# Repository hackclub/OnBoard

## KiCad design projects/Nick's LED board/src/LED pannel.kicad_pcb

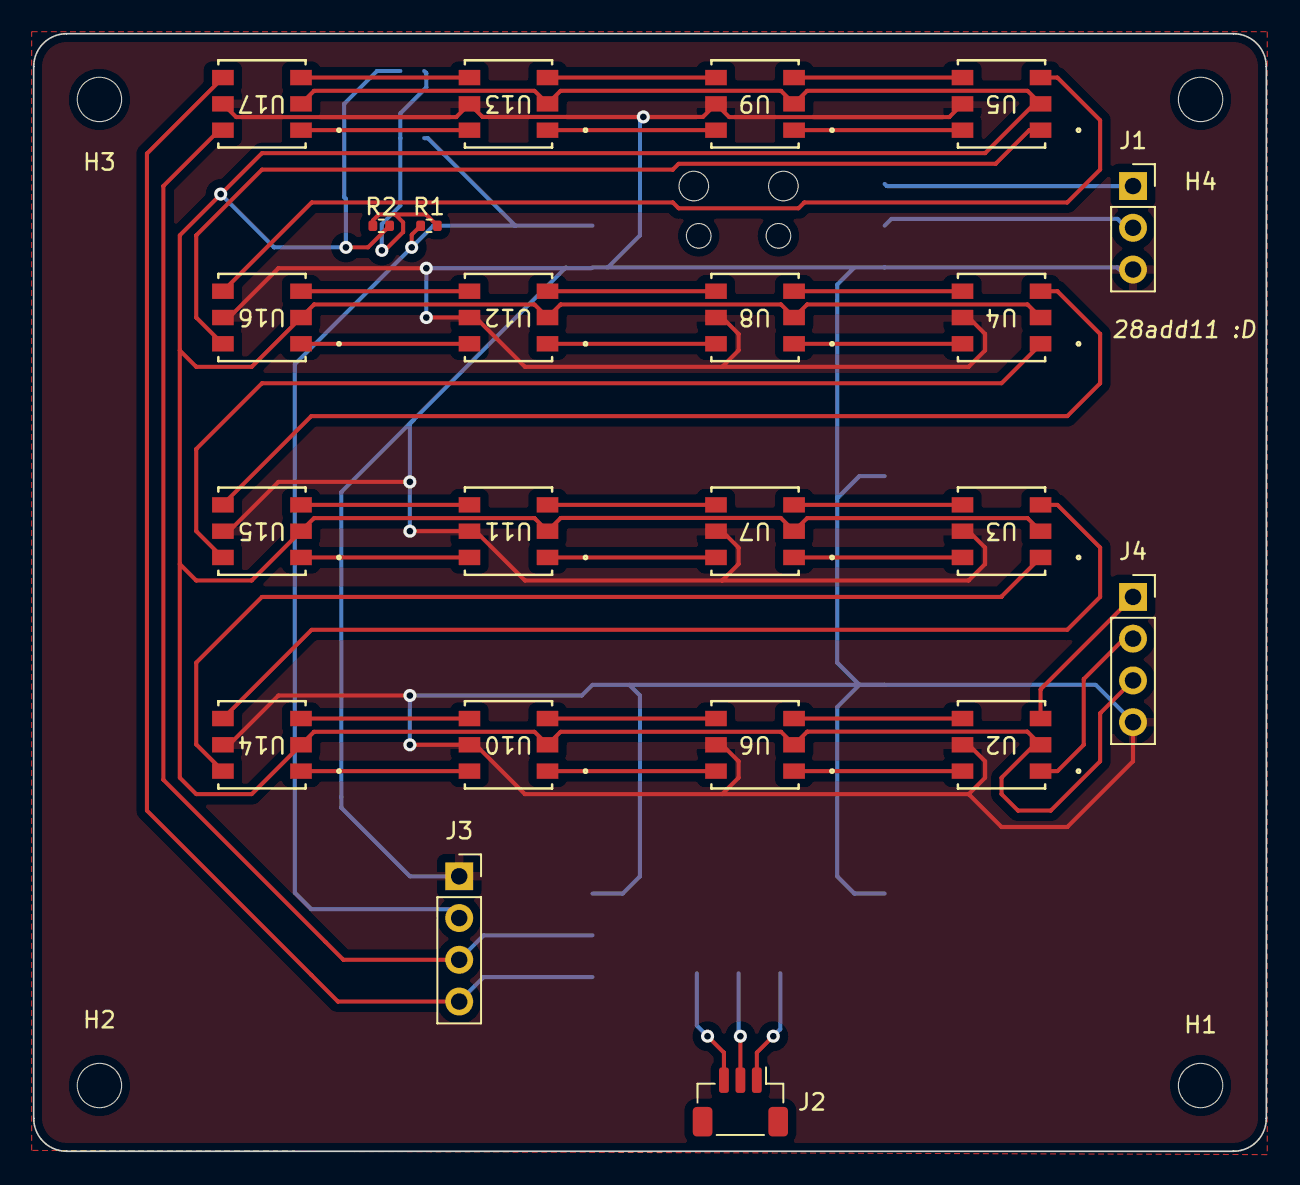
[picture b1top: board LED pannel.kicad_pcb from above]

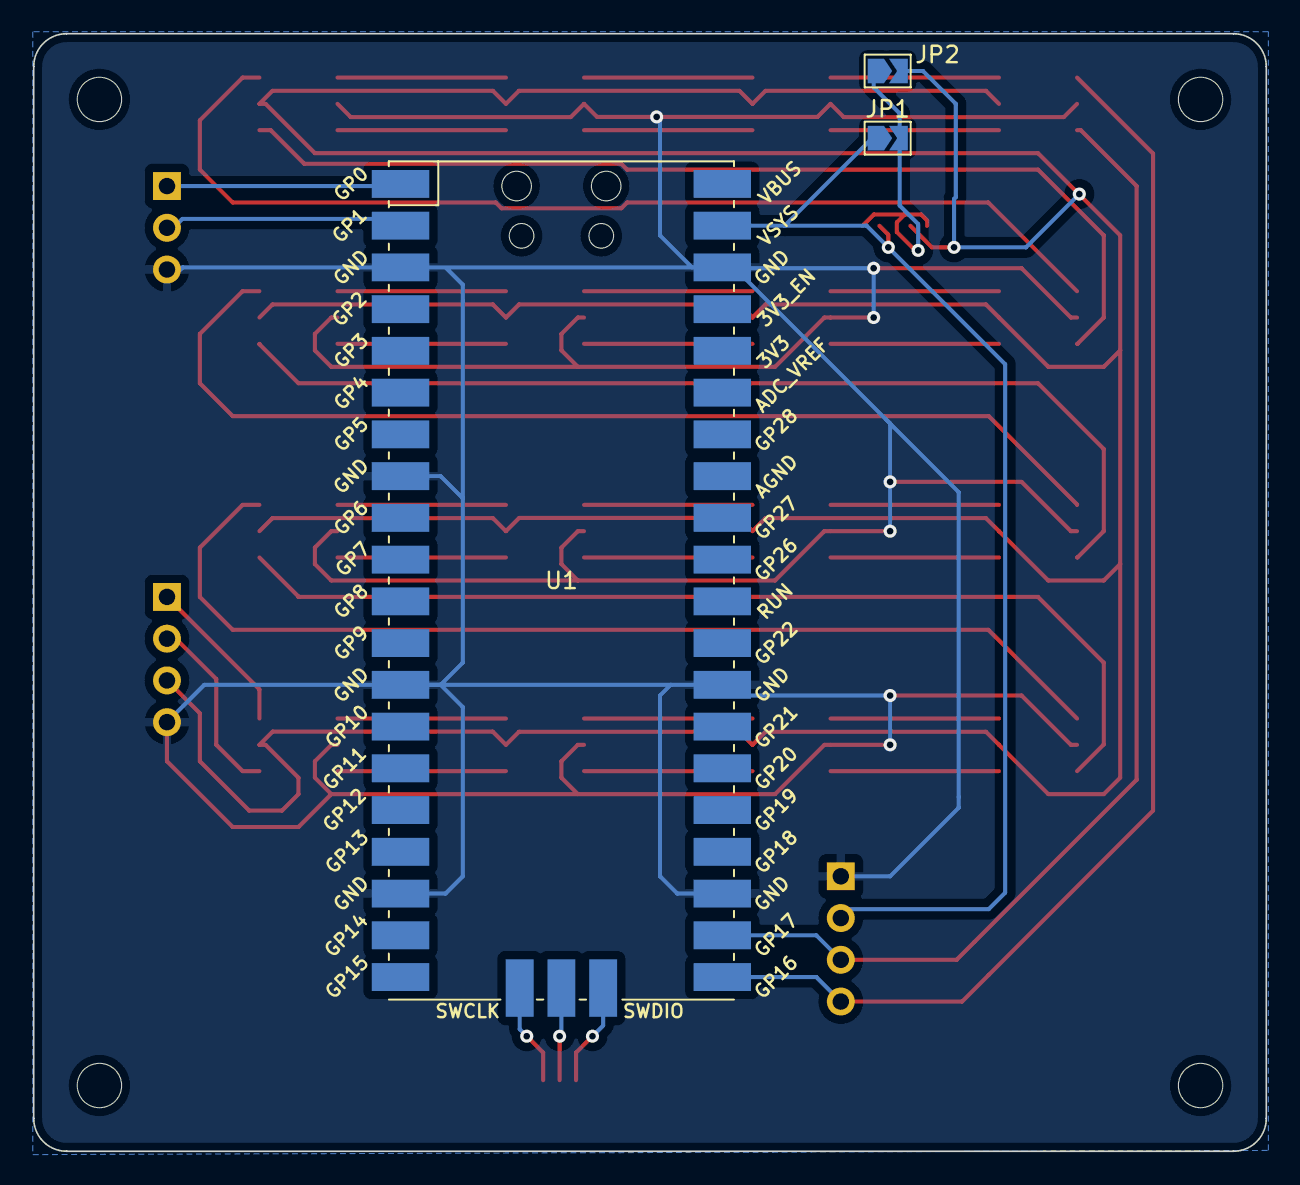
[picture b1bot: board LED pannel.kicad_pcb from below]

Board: 2 copper layers, 75.0 x 68.0 mm, 29 parts (3 on the bottom side), 43 nets.

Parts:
H1, H2, H3, H4: MountingHole; MountingHole_2.7mm
J1: Conn_01x03_Female; PinSocket_1x03_P2.54mm_Vertical
J2: Conn_01x03_Female; JST_SH_BM03B-SRSS-TB_1x03-1MP_P1.00mm_Vertical
J3, J4: Conn_01x04_Female; PinSocket_1x04_P2.54mm_Vertical
JP1, JP2: SolderJumper_2_Open; SolderJumper-2_P1.3mm_Open_TrianglePad1.0x1.5mm
R1, R2: 220ohm; R_0402_1005Metric
U1: RPI-Pico; RPi_Pico_SMD
U2, U3, U4, U5, U6, U7, U8, U9, U10, U11, U12, U13, U14, U15, U16, U17: 601000200; DFN6_601000_SEE

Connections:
/Backup in: J3.3, U1.22 (GPIO17), U17.6 (BI)
/Brightness control: J4.3, JP2.2 (B), R2.2, U2.2 (VCC), U3.2 (VCC), U4.2 (VCC), U5.2 (VCC), U6.2 (VCC), U7.2 (VCC), U8.2 (VCC), U9.2 (VCC), U10.2 (VCC), U11.2 (VCC), U12.2 (VCC), U13.2 (VCC), U14.2 (VCC), U15.2 (VCC), U16.2 (VCC), U17.2 (VCC)
/Data in: J3.4, U1.21 (GPIO16), U17.4 (DI)
/SWD: J2.3, U1.43 (SWDIO)
/UART RX: J1.2, U1.2 (GPIO1)
/UART TX: J1.1, U1.1 (GPIO0)
GND: J1.3, J3.1, J4.4, U1.3 (GND), U1.8 (GND), U1.13 (GND), U1.18 (GND), U1.23 (GND), U1.28 (GND), U1.38 (GND), U2.5 (GND), U3.5 (GND), U4.5 (GND), U5.5 (GND), U6.5 (GND), U7.5 (GND), U8.5 (GND), U9.5 (GND), U10.5 (GND), U11.5 (GND), U12.5 (GND), U13.5 (GND), U14.5 (GND), U15.5 (GND), U16.5 (GND), U17.5 (GND)
unnamed: J2.1, U1.41 (SWCLK)
unnamed: J2.2, U1.42 (GND)
unnamed: J4.1, U2.3 (DO)
unnamed: J4.2, U2.1 (BO)
unnamed: JP1.2 (B), JP2.1 (A), R1.2, R2.1
unnamed: U2.4 (DI), U6.3 (DO)
unnamed: U2.6 (BI), U6.1 (BO)
unnamed: U3.4 (DI), U7.3 (DO)
unnamed: U3.6 (BI), U7.1 (BO)
unnamed: U4.4 (DI), U8.3 (DO)
unnamed: U4.6 (BI), U8.1 (BO)
unnamed: U5.4 (DI), U9.3 (DO)
unnamed: U5.6 (BI), U9.1 (BO)
unnamed: U6.6 (BI), U10.1 (BO)
unnamed: U6.4 (DI), U10.3 (DO)
unnamed: U10.4 (DI), U14.3 (DO)
unnamed: U10.6 (BI), U14.1 (BO)
unnamed: U7.6 (BI), U11.1 (BO)
unnamed: U7.4 (DI), U11.3 (DO)
unnamed: U11.4 (DI), U15.3 (DO)
unnamed: U11.6 (BI), U15.1 (BO)
unnamed: U8.6 (BI), U12.1 (BO)
unnamed: U8.4 (DI), U12.3 (DO)
unnamed: U12.4 (DI), U16.3 (DO)
unnamed: U12.6 (BI), U16.1 (BO)
unnamed: U9.6 (BI), U13.1 (BO)
unnamed: U9.4 (DI), U13.3 (DO)
unnamed: U13.4 (DI), U17.3 (DO)
unnamed: U13.6 (BI), U17.1 (BO)
unnamed: U3.3 (DO), U14.4 (DI)
unnamed: U3.1 (BO), U14.6 (BI)
unnamed: U4.3 (DO), U15.4 (DI)
unnamed: U4.1 (BO), U15.6 (BI)
unnamed: U5.3 (DO), U16.4 (DI)
unnamed: U5.1 (BO), U16.6 (BI)
VCC: J3.2, JP1.1 (A), R1.1, U1.39 (VSYS)

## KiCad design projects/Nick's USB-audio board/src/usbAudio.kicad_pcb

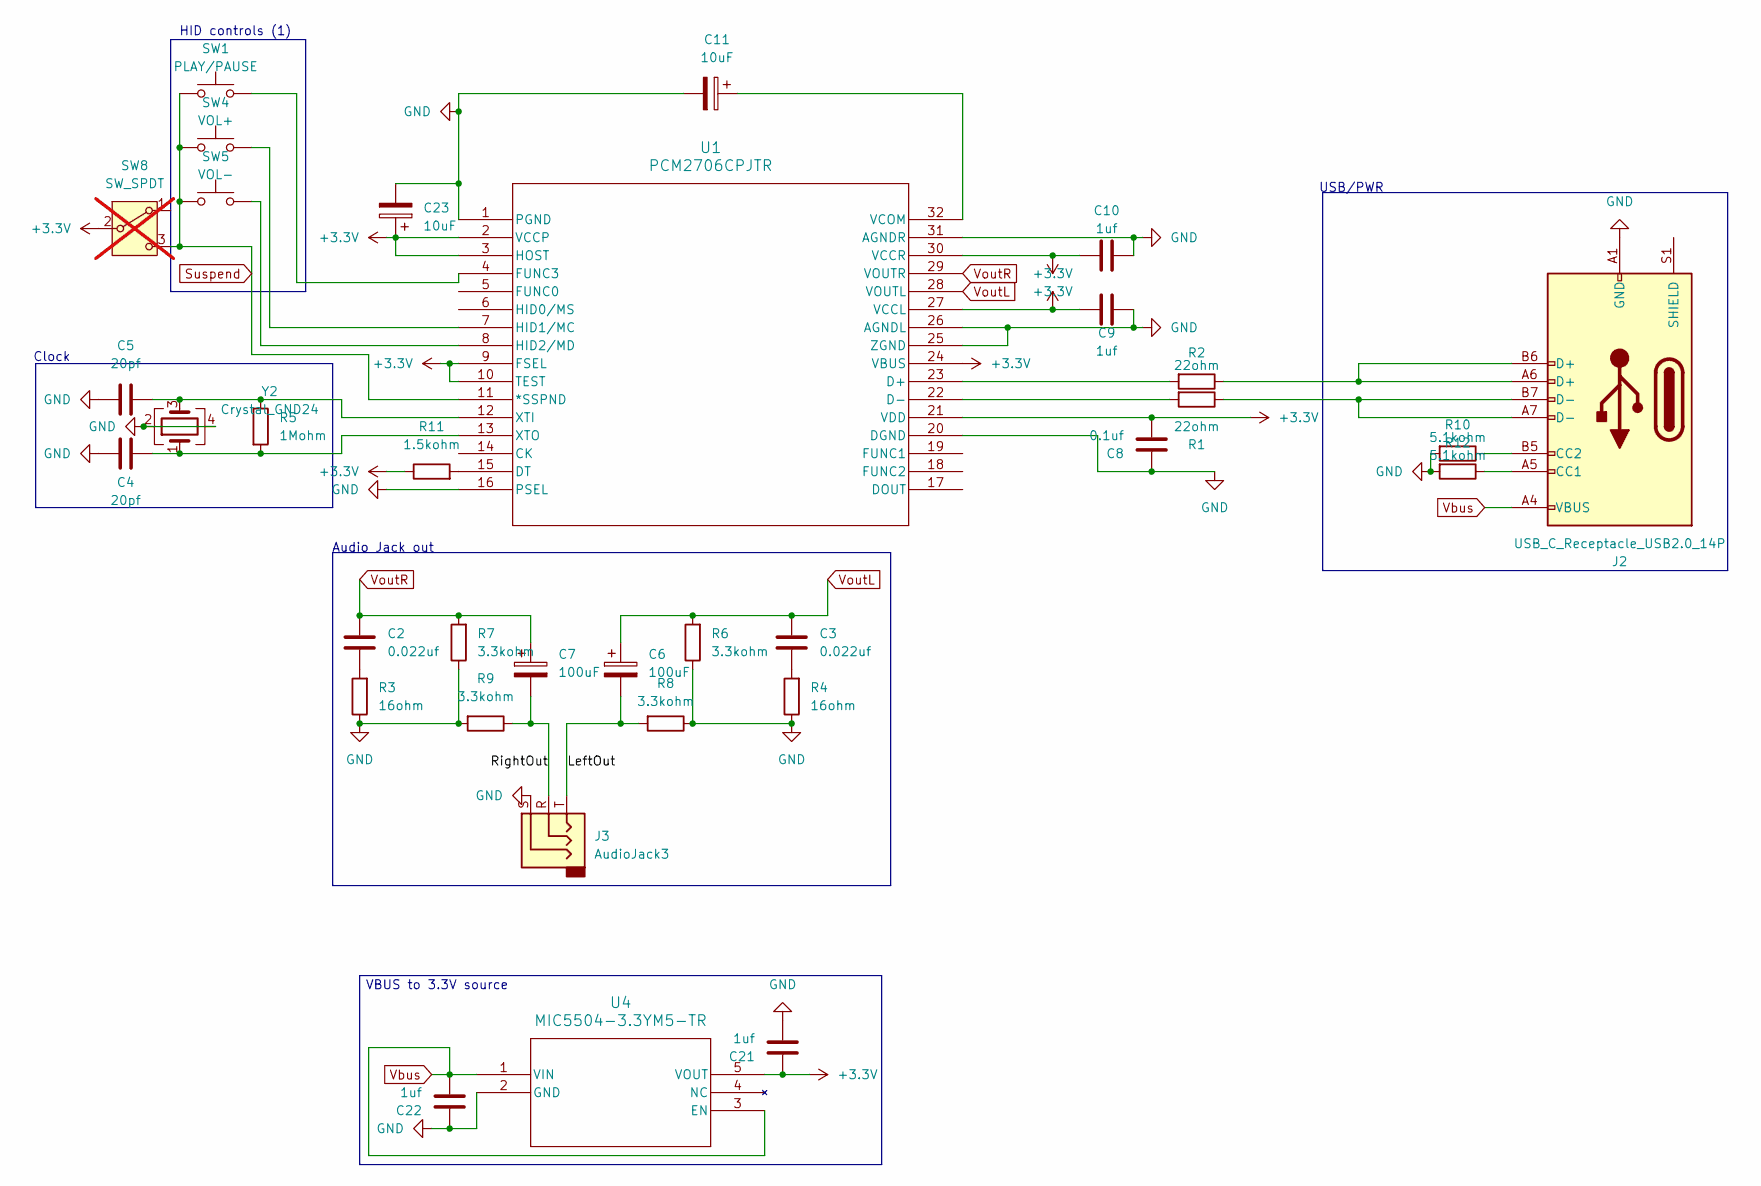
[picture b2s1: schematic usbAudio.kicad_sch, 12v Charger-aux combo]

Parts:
C2, C3: 0.022uf; C_0805_2012Metric_Pad1.18x1.45mm_HandSolder; LCSC Part # C107147
C4, C5: 20pf; C_0603_1608Metric_Pad1.08x0.95mm_HandSolder; LCSC Part # C105621
C6, C7: 100uF; CP_Radial_D6.3mm_P2.50mm; LCSC Part # C109392
C8: 0.1uf; C_0603_1608Metric_Pad1.08x0.95mm_HandSolder; LCSC Part # C14663
C9, C10, C21, C22: 1uf; C_0603_1608Metric_Pad1.08x0.95mm_HandSolder; LCSC Part # C1592
C11, C23: 10uF; CP_Radial_D5.0mm_P2.00mm; LCSC Part # C250876
J2: USB_C_Receptacle_USB2.0_14P; USB_C_Receptacle_HCTL_HC-TYPE-C-16P-01A; LCSC Part # C2894897
J3: AudioJack3; Jack_3.5mm_KoreanHropartsElec_PJ-320D-4A_Horizontal_copy; LCSC Part # C95562
R1, R2: 22ohm; R_0603_1608Metric_Pad0.98x0.95mm_HandSolder; LCSC Part # C23345
R3, R4: 16ohm; R_0603_1608Metric_Pad0.98x0.95mm_HandSolder; LCSC Part # C25185
R5: 1Mohm; R_0603_1608Metric_Pad0.98x0.95mm_HandSolder; LCSC Part # C22935
R6, R7, R8, R9: 3.3kohm; R_0603_1608Metric_Pad0.98x0.95mm_HandSolder; LCSC Part # C22978
R10, R12: 5.1kohm; R_0603_1608Metric_Pad0.98x0.95mm_HandSolder; LCSC Part # C23186
R11: 1.5kohm; R_0603_1608Metric_Pad0.98x0.95mm_HandSolder; LCSC Part # C22843
SW1: PLAY/PAUSE; SW_PUSH_6mm_H4.3mm; LCSC Part # C97440
SW4: VOL+; SW_PUSH_6mm_H4.3mm; LCSC Part # C97440
SW5: VOL-; SW_PUSH_6mm_H4.3mm; LCSC Part # C97440
SW8: SW_SPDT; SW_JS102011SAQN_Xoverhang; not fitted
U1: PCM2706CPJTR; PJT32; LCSC Part # C2651268
U4: MIC5504-3.3YM5-TR; SOT-23-5_MC_MCH; LCSC Part # C88419
Y2: Crystal_GND24; Crystal_SMD_3225-4Pin_3.2x2.5mm_HandSoldering; LCSC Part # C9002

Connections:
+3.3V: C8.1, C9.1, C10.1, C21.2, C23.1, R11.1, SW8.2 (B), U1.2 (VCCP), U1.3 (HOST), U1.9 (FSEL), U1.10 (TEST), U1.21 (VDD), U1.24 (VBUS), U1.27 (VCCL), U1.30 (VCCR), U4.5 (VOUT)
/LeftOut: C6.2, J3.T, R8.2
/RightOut: C7.2, J3.R, R9.1
GND: C4.2, C5.2, C8.2, C9.2, C10.2, C11.2, C21.1, C22.2, C23.2, J2.A1 (GND), J2.A12 (GND), J2.B1 (GND), J2.B12 (GND), J3.S, R3.1, R4.1, R6.1, R7.1, R8.1, R9.2, R10.2, R12.2, U1.1 (PGND), U1.16 (PSEL), U1.20 (DGND), U1.25 (ZGND), U1.26 (AGNDL), U1.31 (AGNDR), U4.2 (GND), Y2.2, Y2.4
unnamed: C2.1, R3.2
unnamed: C3.1, R4.2
unnamed: J2.A5 (CC1), R12.1
unnamed: J2.B5 (CC2), R10.1
unnamed: J2.A6 (D+), J2.B6 (D+), R2.1
unnamed: J2.A7 (D-), J2.B7 (D-), R1.1
unnamed: R2.2, U1.23 (D+)
unnamed: R1.2, U1.22 (D-)
unnamed: R11.2, U1.15 (DT)
unnamed: SW1.2, U1.4 (FUNC3)
unnamed: SW4.2, U1.7 (HID1/MC)
unnamed: SW5.2, U1.8 (HID2/MD)
unnamed: C11.1, U1.32 (VCOM)
unnamed: C5.1, R5.1, U1.12 (XTI), Y2.3
unnamed: C4.1, R5.2, U1.13 (XTO), Y2.1
Suspend: SW1.1, SW4.1, SW5.1, SW8.3 (C), U1.11 (*SSPND)
Vbus: C22.1, J2.A4 (VBUS), J2.A9 (VBUS), J2.B4 (VBUS), J2.B9 (VBUS), U4.1 (VIN), U4.3 (EN)
VoutL: C3.2, C6.1, R6.2, U1.28 (VOUTL)
VoutR: C2.2, C7.1, R7.2, U1.29 (VOUTR)

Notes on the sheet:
USB/PWR
HID controls (1)
Audio Jack out
Clock
VBUS to 3.3V source

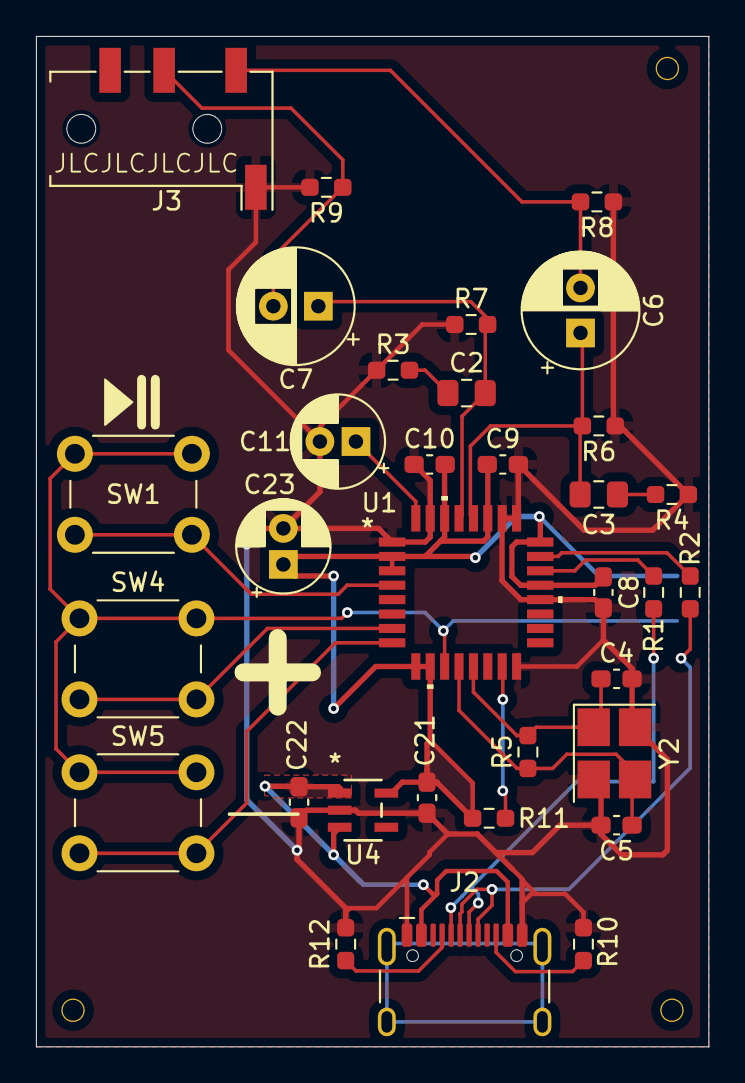
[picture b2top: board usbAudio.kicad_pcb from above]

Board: 2 copper layers, 37.4 x 56.1 mm, 34 parts (1 on the bottom side), 23 nets.

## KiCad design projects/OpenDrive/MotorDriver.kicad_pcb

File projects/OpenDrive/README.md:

---
name: "Isaac Wardell"
slack_handle: "@IceChes"
github_handle: "@IceChes"
project: "OpenDrive"

---

# OpenDrive
## Summary
##### Compact, inexpensive, open source motor controller for 1lb combat robots. Capable of controlling 2 motors and providing 5V BEC power. Uses the servo protocol.

## Plan
##### This is a roughly $35 board with one-sided assembly. The OpenDrive PCB was designed to be mostly user-solderable.

## Design
##### Thanks to Hack Club and NHRL. Designed in KiCad 7.0.

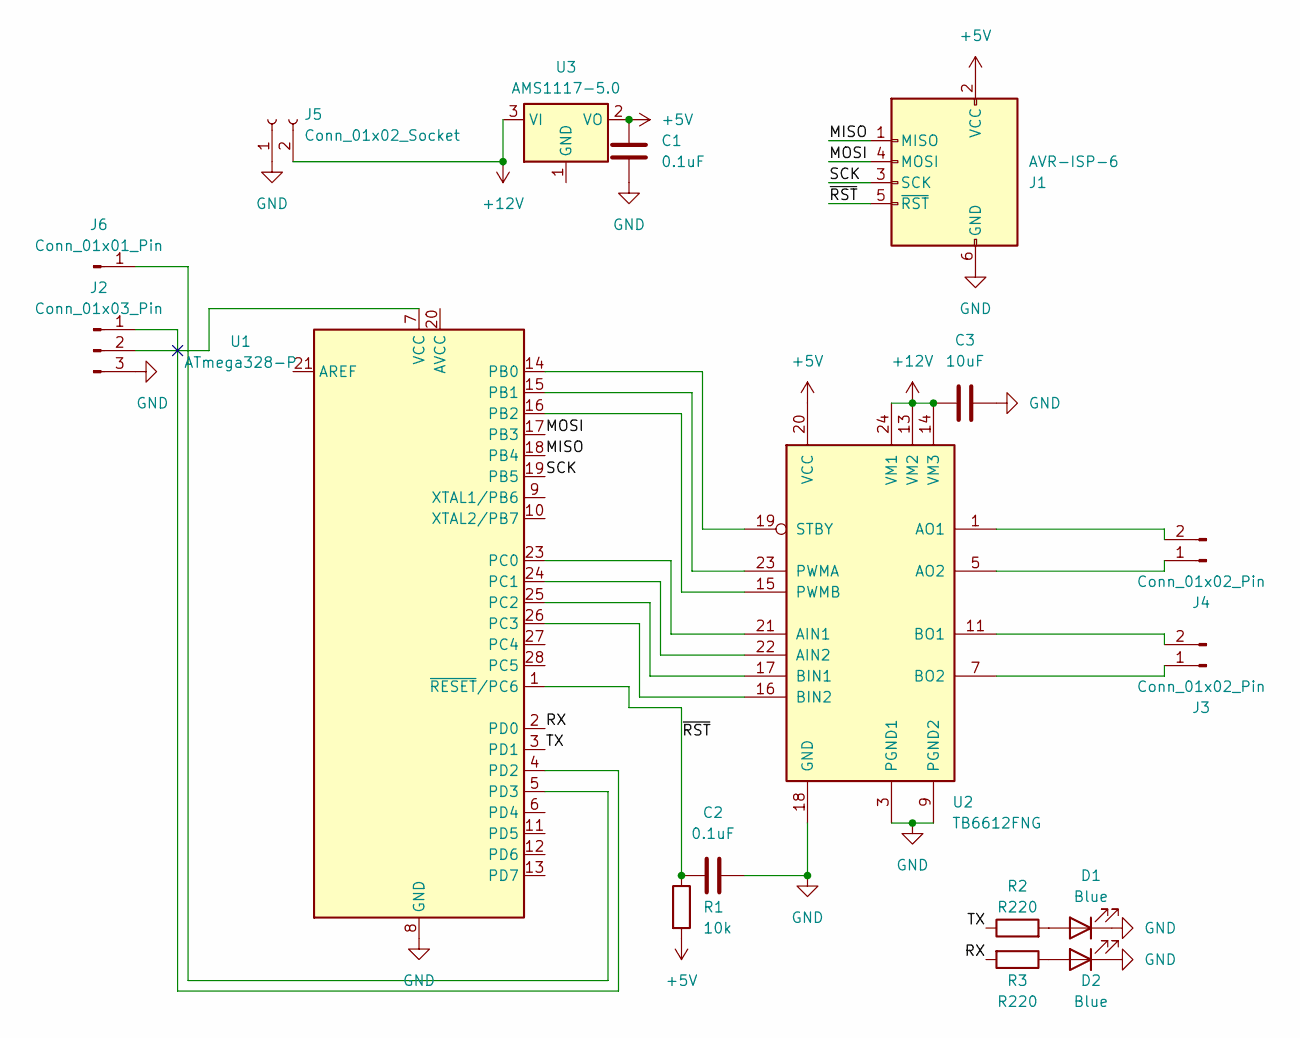
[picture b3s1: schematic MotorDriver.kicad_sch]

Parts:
C1, C2: 0.1uF; C_0805_2012Metric
C3: 10uF; C_0805_2012Metric
D1, D2: Blue; LED_0805_2012Metric
J1: AVR-ISP-6; PinHeader_2x03_P2.54mm_Vertical
J2: Conn_01x03_Pin; PinHeader_1x03_P2.54mm_Vertical
J3, J4: Conn_01x02_Pin; PinHeader_1x02_P2.54mm_Vertical
J5: Conn_01x02_Socket; PinSocket_1x02_P2.54mm_Vertical
J6: Conn_01x01_Pin; PinSocket_1x01_P2.54mm_Vertical
R1: 10k; R_0805_2012Metric
R2, R3: R220; R_0805_2012Metric
U1: ATmega328-P; TQFP-32_7x7mm_P0.8mm; LCSC C14877
U2: TB6612FNG; SSOP-24_5.3x8.2mm_P0.65mm; LCSC C88224
U3: AMS1117-5.0; SOT-223-3_TabPin2; LCSC C351787

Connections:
+5V: C1.1, J1.2 (VCC), R1.2, U2.20 (VCC), U3.2 (VO)
+12V: C3.1, J5.2, U2.13 (VM2), U2.14 (VM3), U2.24 (VM1), U3.3 (VI)
/MISO: J1.1 (MISO), U1.18 (PB4)
/MOSI: J1.4 (MOSI), U1.17 (PB3)
/RX: R3.2, U1.2 (PD0)
/SCK: J1.3 (SCK), U1.19 (PB5)
/TX: R2.1, U1.3 (PD1)
/~RST: C2.1, J1.5 (~RST), R1.1, U1.1 (~RESET/PC6)
GND: C1.2, C2.2, C3.2, D1.1 (K), D2.1 (K), J1.6 (GND), J2.3, J5.1, U1.8 (GND), U1.22 (GND), U2.3 (PGND1), U2.4 (PGND1), U2.9 (PGND2), U2.10 (PGND2), U2.18 (GND)
unnamed: D1.2 (A), R2.2
unnamed: D2.2 (A), R3.1
unnamed: J2.1, U1.4 (PD2)
unnamed: J2.2, U1.7 (VCC)
unnamed: J3.1, U2.7 (BO2), U2.8 (BO2)
unnamed: J3.2, U2.11 (BO1), U2.12 (BO1)
unnamed: J4.1, U2.5 (AO2), U2.6 (AO2)
unnamed: J4.2, U2.1 (AO1), U2.2 (AO1)
unnamed: J6.1, U1.5 (PD3)
unnamed: U1.14 (PB0), U2.19 (STBY)
unnamed: U1.15 (PB1), U2.23 (PWMA)
unnamed: U1.16 (PB2), U2.15 (PWMB)
unnamed: U1.23 (PC0), U2.21 (AIN1)
unnamed: U1.24 (PC1), U2.22 (AIN2)
unnamed: U1.25 (PC2), U2.17 (BIN1)
unnamed: U1.26 (PC3), U2.16 (BIN2)

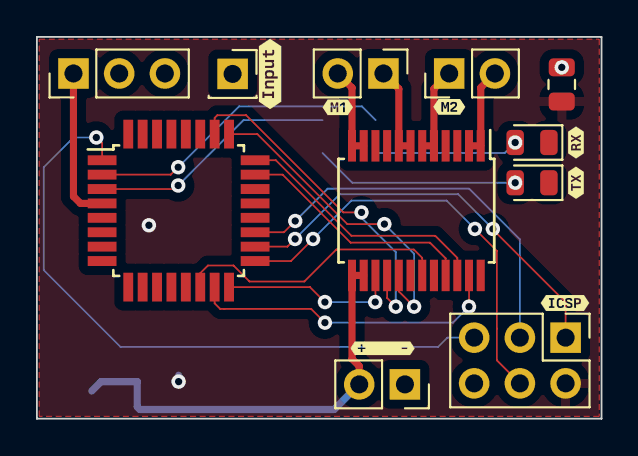
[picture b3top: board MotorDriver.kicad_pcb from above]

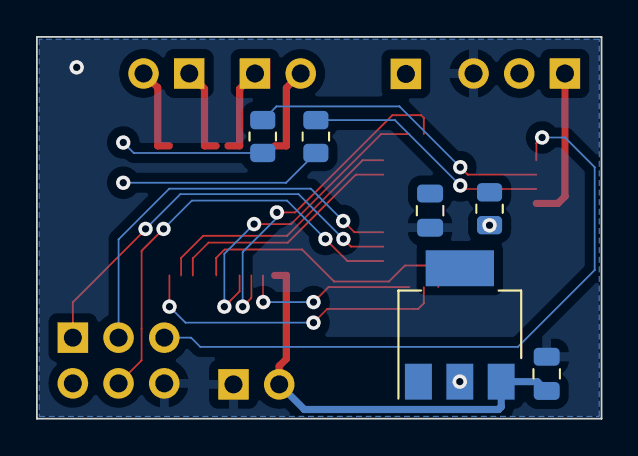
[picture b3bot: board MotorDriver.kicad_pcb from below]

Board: 2 copper layers, 31.4 x 21.2 mm, 24 parts (6 on the bottom side), 25 nets.

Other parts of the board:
kibuzzard-64EBAE1C: G***; kibuzzard-64EBAE1C
kibuzzard-64EBAE9C: G***; kibuzzard-64EBAE9C
kibuzzard-64EBAE69: G***; kibuzzard-64EBAE69
kibuzzard-64EBAE70: G***; kibuzzard-64EBAE70
kibuzzard-64EBAE89: G***; kibuzzard-64EBAE89
kibuzzard-64EBAEB9: G***; kibuzzard-64EBAEB9
kibuzzard-64EBAEC6: G***; kibuzzard-64EBAEC6

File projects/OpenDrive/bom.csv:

Designator,Footprint,Quantity,Value,LCSC Part #
"C1, C2",0805,2,0.1uF,
C3,0805,1,10uF,
"D1, D2",0805,2,Blue,
J1,PinHeader_2x03_P2.54mm_Vertical,1,AVR-ISP-6,
J2,PinHeader_1x03_P2.54mm_Vertical,1,Conn_01x03_Pin,
"J3, J4",PinHeader_1x02_P2.54mm_Vertical,2,Conn_01x02_Pin,
J5,PinSocket_1x02_P2.54mm_Vertical,1,Conn_01x02_Socket,
J6,PinSocket_1x01_P2.54mm_Vertical,1,Conn_01x01_Pin,
R1,0805,1,10k,
"R2, R3",0805,2,R220,
U1,TQFP-32_7x7mm_P0.8mm,1,ATmega328-P,C14877
U2,SSOP-24_5.3x8.2mm_P0.65mm,1,TB6612FNG,C88224
U3,SOT-223-3_TabPin2,1,AMS1117-5.0,C351787

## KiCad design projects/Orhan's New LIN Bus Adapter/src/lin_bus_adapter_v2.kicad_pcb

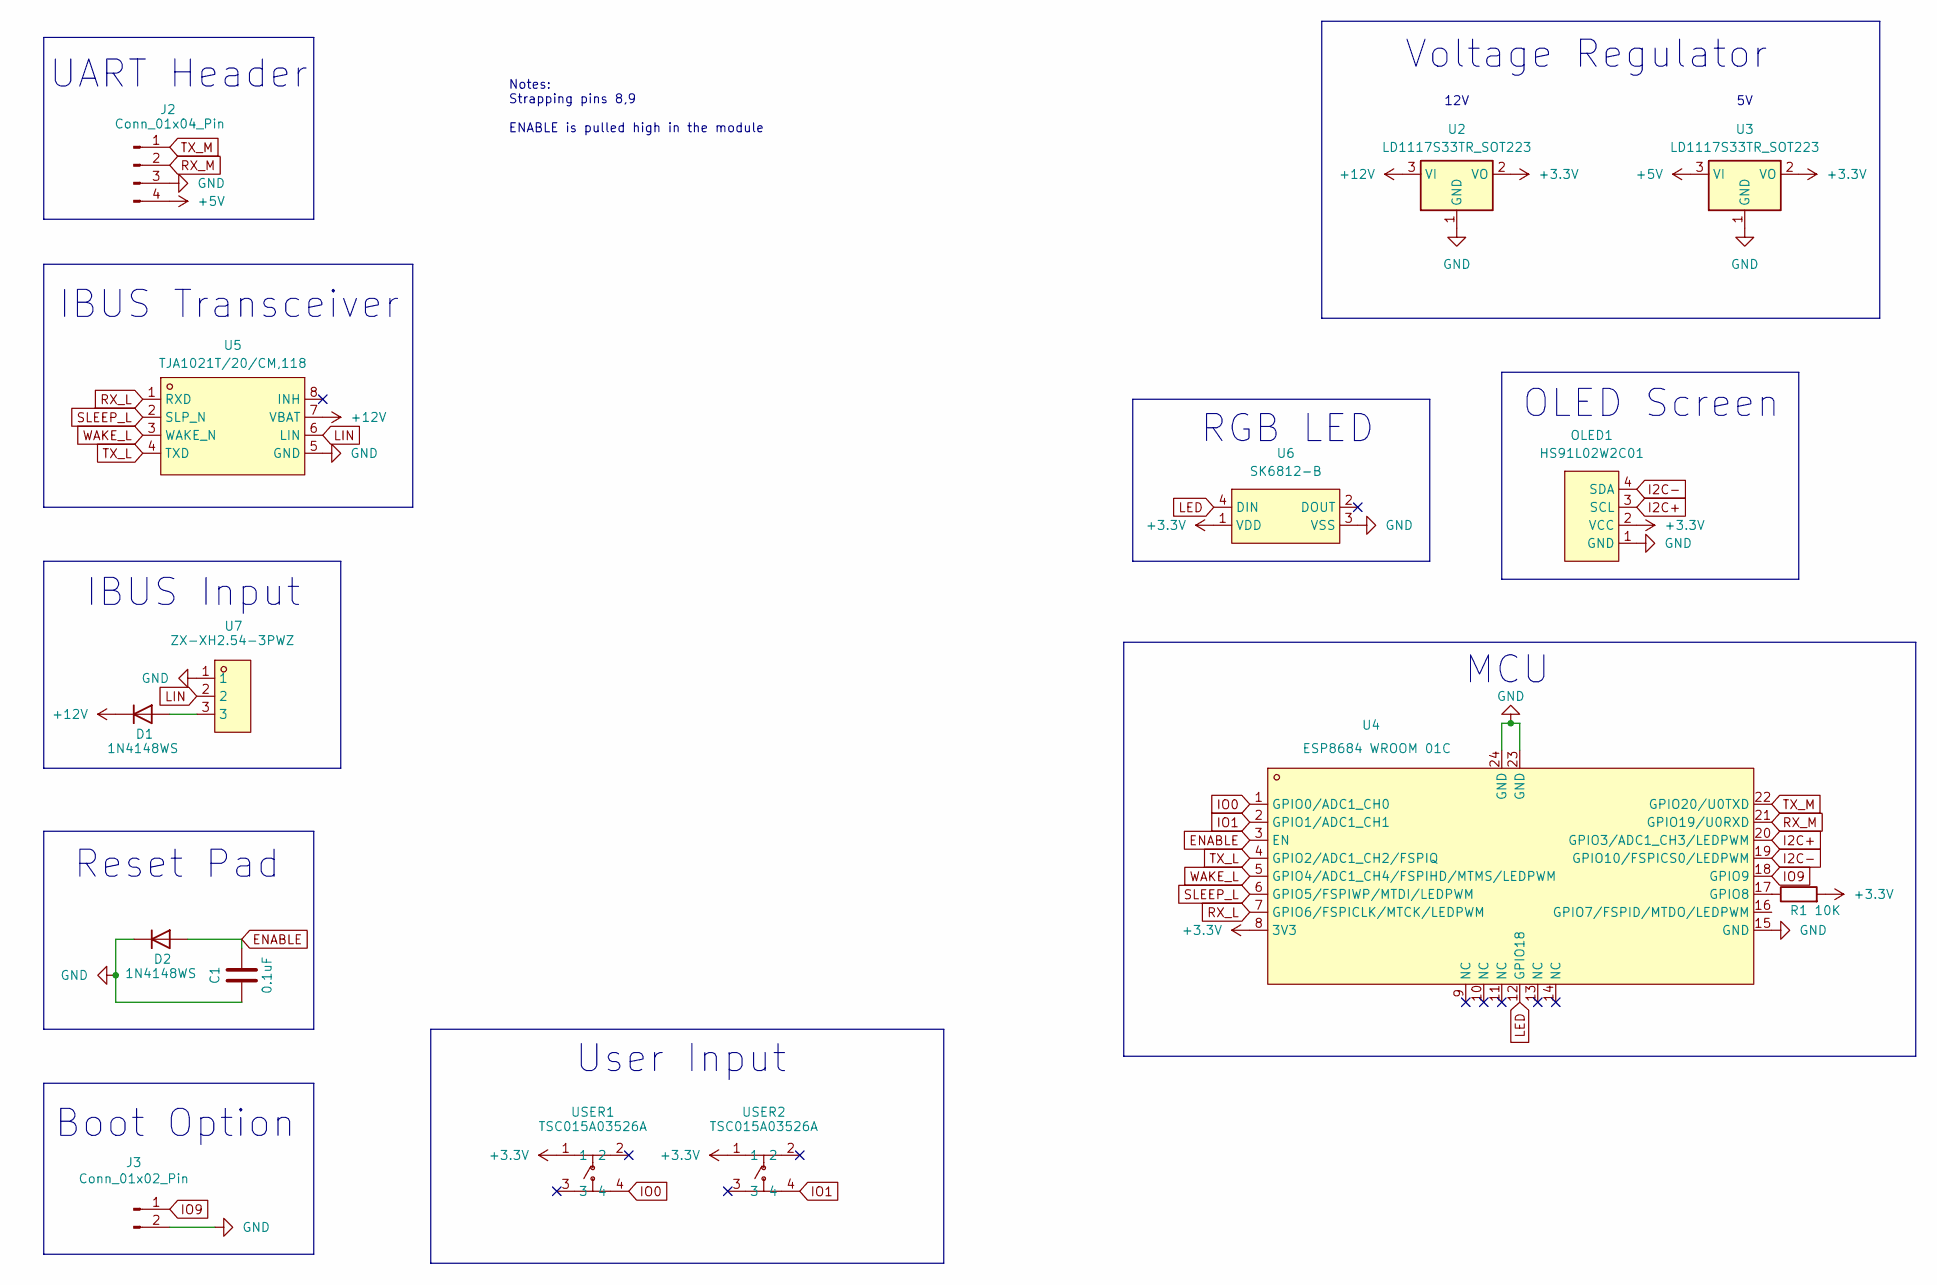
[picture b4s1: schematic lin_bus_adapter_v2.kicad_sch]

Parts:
C1: 0.1uF; C_0805_2012Metric_Pad1.18x1.45mm_HandSolder
D1, D2: 1N4148WS; D_SOD-323_HandSoldering
J2: Conn_01x04_Pin; PinHeader_1x04_P2.54mm_Vertical
J3: Conn_01x02_Pin; PinHeader_1x02_P2.54mm_Vertical
OLED1: HS91L02W2C01; OLED-TH_L38.0-W12.0_HS91L02W2C01; LCSC Part C5248081
R1: 10K; R_0805_2012Metric_Pad1.20x1.40mm_HandSolder
U2, U3: LD1117S33TR_SOT223; SOT-223-3_TabPin2
U4: ESP8684 WROOM 01C; WIRELM-SMD_ESP8684-WROOM0-1C; LCSC Part C9900074922
U5: TJA1021T/20/CM,118; SOIC-8_L4.9-W3.9-P1.27-LS6.0-BL; LCSC Part C128810
U6: SK6812-B; LED-SMD_4P-L5.0-W5.0-LS5.4-TL-1; LCSC Part C5380881
U7: ZX-XH2.54-3PWZ; HDR-TH_3P-P2.50_ZX-XH2.54-3PWZ; LCSC Part C7429642
USER1, USER2: TSC015A03526A; SW-SMD_4P-L4.5-W4.5-P3.00-LS6.8; LCSC Part C2888900

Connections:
+3.3V: OLED1.2 (VCC), R1.2, U2.2 (VO), U3.2 (VO), U4.8 (3V3), U6.1 (VDD), USER1.1, USER2.1
+5V: J2.4, U3.3 (VI)
+12V: D1.1 (K), U2.3 (VI), U5.7 (VBAT)
ENABLE: C1.1, D2.2 (A), U4.3 (EN)
GND: C1.2, D2.1 (K), J2.3, J3.2, OLED1.1 (GND), U2.1 (GND), U3.1 (GND), U4.15 (GND), U4.23 (GND), U4.24 (GND), U5.5 (GND), U6.3 (VSS), U7.1
I2C+: OLED1.3 (SCL), U4.20 (GPIO3/ADC1_CH3/LEDPWM)
I2C-: OLED1.4 (SDA), U4.19 (GPIO10/FSPICS0/LEDPWM)
IO0: U4.1 (GPIO0/ADC1_CH0), USER1.4
IO1: U4.2 (GPIO1/ADC1_CH1), USER2.4
IO9: J3.1, U4.18 (GPIO9)
LED: U4.12 (GPIO18), U6.4 (DIN)
LIN: U5.6 (LIN), U7.2
unnamed: D1.2 (A), U7.3
unnamed: R1.1, U4.17 (GPIO8)
RX_L: U4.7 (GPIO6/FSPICLK/MTCK/LEDPWM), U5.1 (RXD)
RX_M: J2.2, U4.21 (GPIO19/U0RXD)
SLEEP_L: U4.6 (GPIO5/FSPIWP/MTDI/LEDPWM), U5.2 (SLP_N)
TX_L: U4.4 (GPIO2/ADC1_CH2/FSPIQ), U5.4 (TXD)
TX_M: J2.1, U4.22 (GPIO20/U0TXD)
WAKE_L: U4.5 (GPIO4/ADC1_CH4/FSPIHD/MTMS/LEDPWM), U5.3 (WAKE_N)

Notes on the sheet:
UART Header
12V
Voltage Regulator
IBUS Transceiver
RGB LED
IBUS Input
OLED Screen
Reset Pad
MCU
User Input
Boot Option
Notes: Strapping pins 8,9 ENABLE is pulled high in the module

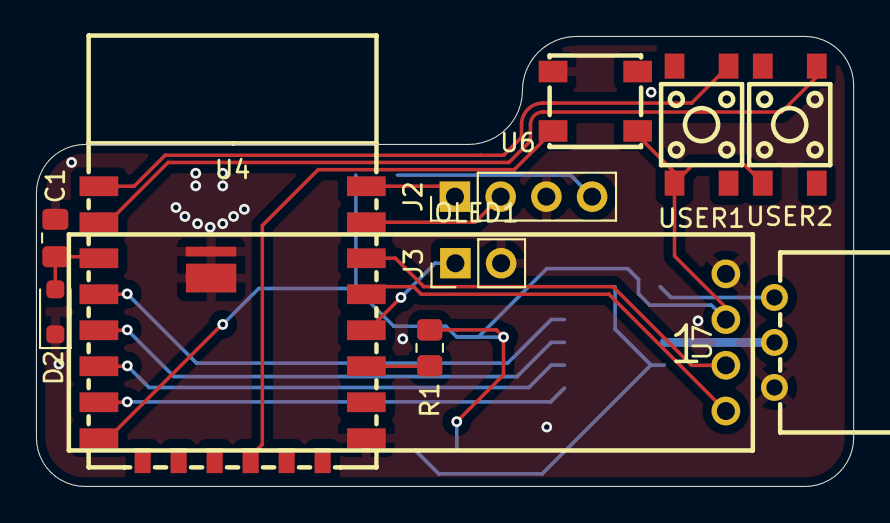
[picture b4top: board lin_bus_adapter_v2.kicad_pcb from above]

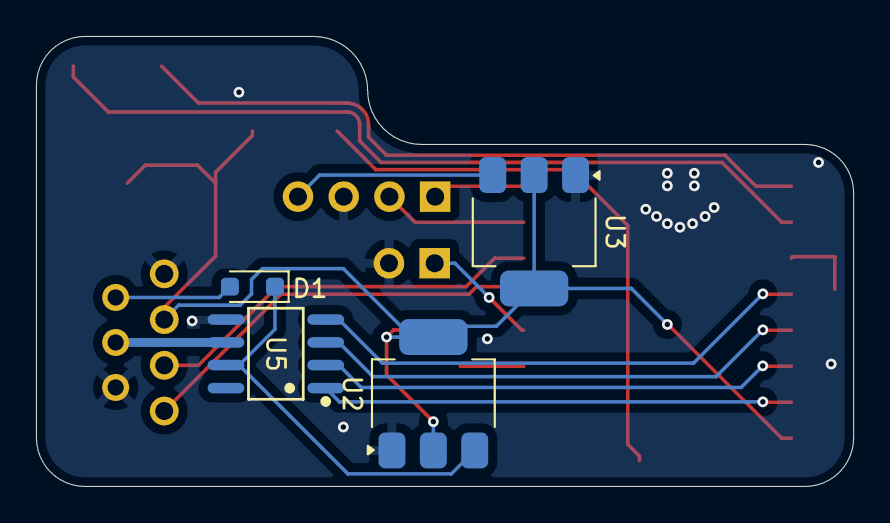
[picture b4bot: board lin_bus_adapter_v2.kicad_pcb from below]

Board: 2 copper layers, 45.4 x 25.0 mm, 15 parts (4 on the bottom side), 20 nets.

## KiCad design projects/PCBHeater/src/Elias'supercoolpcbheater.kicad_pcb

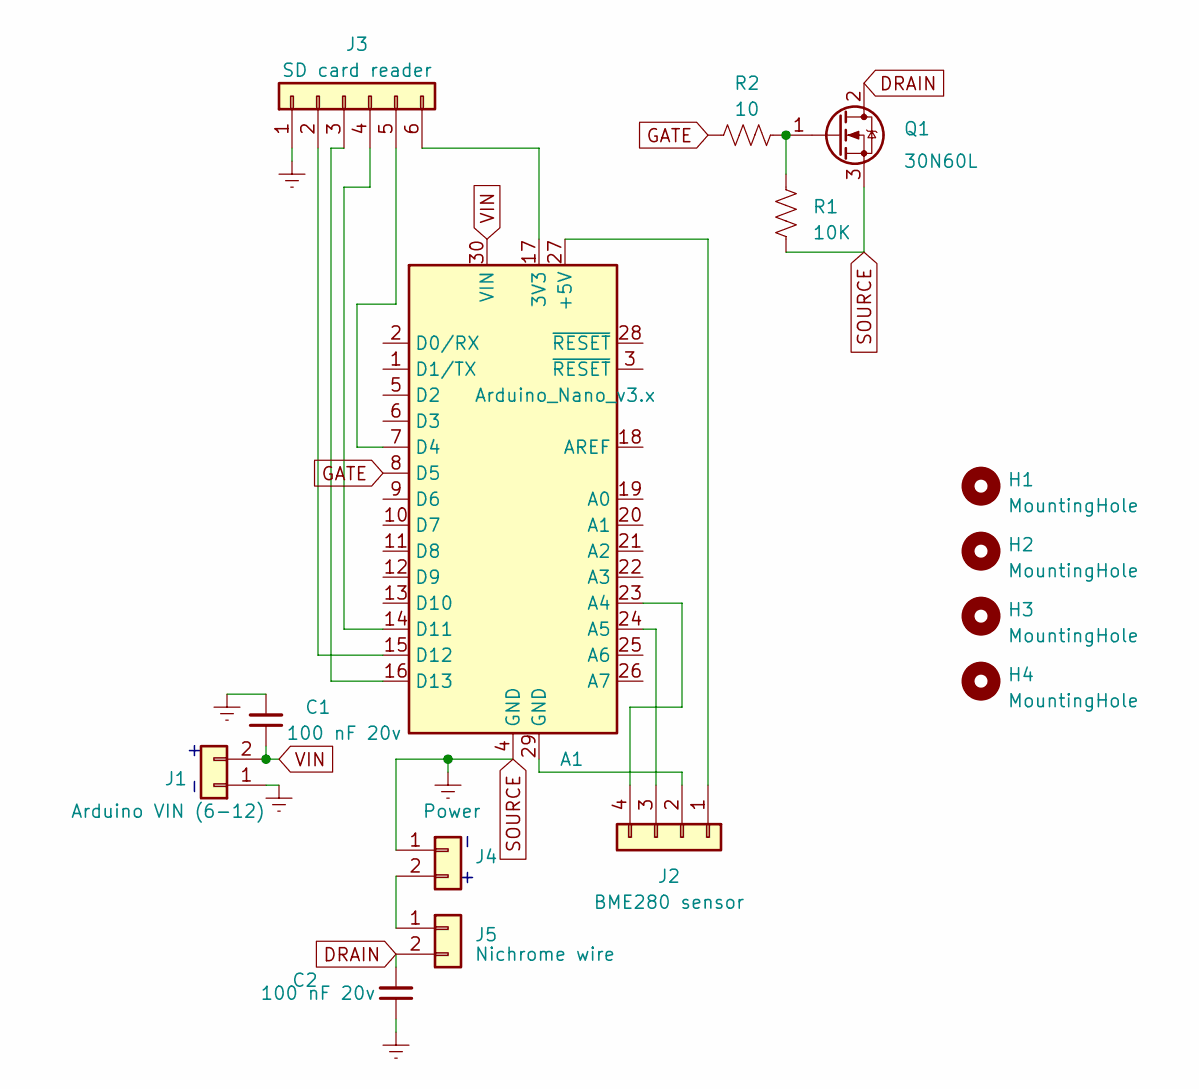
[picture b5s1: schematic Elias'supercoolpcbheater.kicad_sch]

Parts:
A1: Arduino_Nano_v3.x; Arduino_Nano
C1, C2: 100 nF 20v; C_Rect_L10.0mm_W2.5mm_P7.50mm_MKS4
H1, H2, H3, H4: MountingHole; MountingHole_3.2mm_M3
J1: Arduino VIN (6-12); PinHeader_1x02_P2.54mm_Vertical
J2: BME280 sensor; PinHeader_1x04_P2.54mm_Vertical
J3: SD card reader; PinHeader_1x06_P2.54mm_Vertical
J4: Power; PinHeader_1x02_P2.54mm_Vertical
J5: Nichrome wire; PinHeader_1x02_P2.54mm_Vertical
Q1: 30N60L; TO-220-3_Vertical
R1: 10K; R_Axial_DIN0207_L6.3mm_D2.5mm_P10.16mm_Horizontal
R2: 10; R_Axial_DIN0207_L6.3mm_D2.5mm_P10.16mm_Horizontal

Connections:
DRAIN: C2.2, J5.2, Q1.2 (D)
GATE: A1.8 (D5), R2.2
unnamed: A1.17 (3V3), J3.6
unnamed: A1.27 (+5V), J2.1
unnamed: A1.23 (A4), J2.4
unnamed: A1.24 (A5), J2.3
unnamed: A1.7 (D4), J3.5
unnamed: A1.14 (D11), J3.4
unnamed: A1.15 (D12), J3.2
unnamed: A1.16 (D13), J3.3
unnamed: A1.29 (GND), J2.2
unnamed: J4.2, J5.1
unnamed: Q1.1 (G), R1.2, R2.1
SOURCE: A1.4 (GND), C1.2, C2.1, J1.1, J3.1, J4.1, Q1.3 (S), R1.1
VIN: A1.30 (VIN), C1.1, J1.2

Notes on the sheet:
+ -
- +

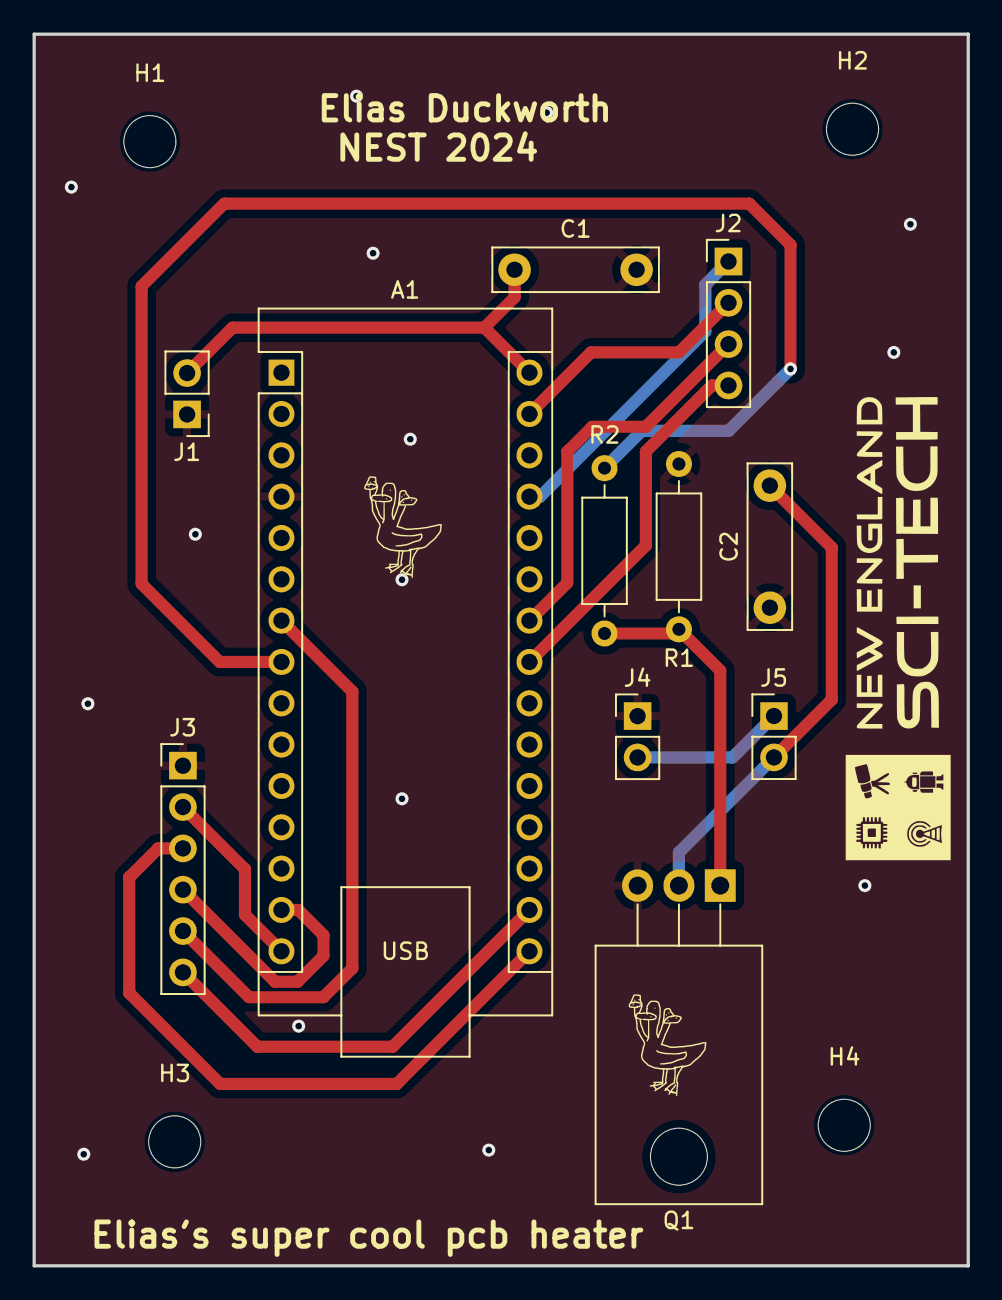
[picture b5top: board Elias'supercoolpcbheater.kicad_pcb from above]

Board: 2 copper layers, 57.4 x 75.7 mm, 15 parts (0 on the bottom side), 15 nets.
